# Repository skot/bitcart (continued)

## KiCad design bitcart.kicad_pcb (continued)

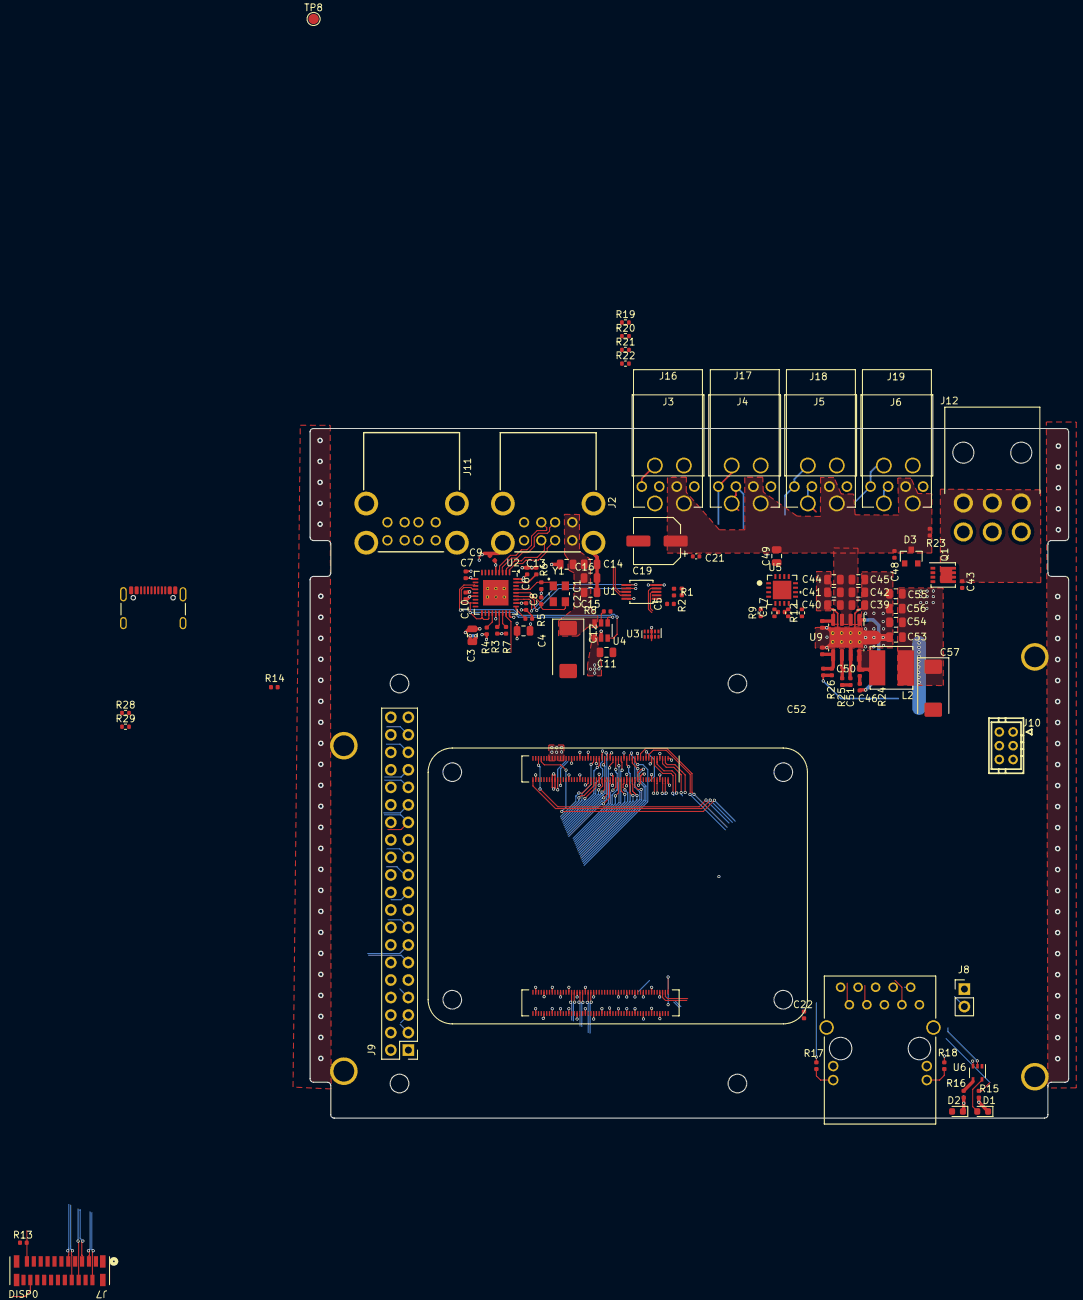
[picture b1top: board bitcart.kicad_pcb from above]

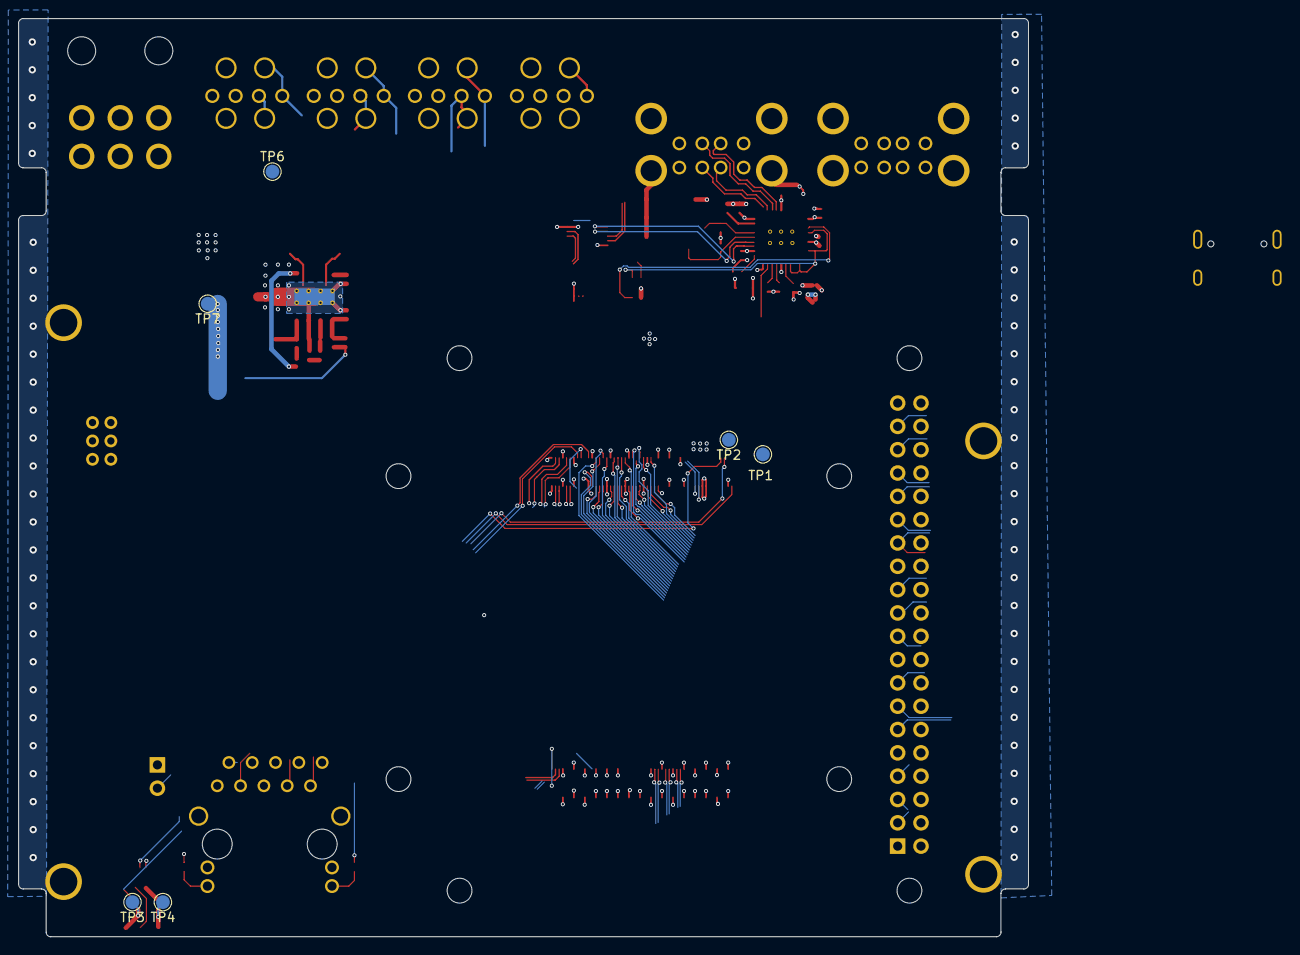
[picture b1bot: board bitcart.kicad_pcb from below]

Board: 4 copper layers, 110.0 x 100.0 mm, 114 parts (6 on the bottom side), 112 nets.

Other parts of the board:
C19: 220uF; CP_Elec_6.3x7.7
C21: 0.1uF; C_0402_1005Metric

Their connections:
/12V: C19.1, C21.1; also elsewhere on the board
GND: C19.2, C21.2; also elsewhere on the board

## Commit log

2023-09-14 initial import -- renamed CM4 IO Board
2023-09-14 added external step files
2023-09-15 removed HDMI, CAM and DISP1 connectors
2023-09-15 added hashboard connectors. added GPU power connector
2023-09-20 extended the board to make room for IO connectors. added the vertical display connector.
2023-09-20 added the PSU control connector.
2023-09-20 remove temp files
2023-10-13 finding/adding digikey part numbers
2023-10-13 added a lot more parts
2023-10-15 added the right board outline. rotated the CM4. switched to single-shroud RA fan connectors
2023-10-15 add render
2023-10-17 resolved some schematic-board errors. switched to tap-on-top ethernet.
2024-02-27 pulled in bitcrane fan and data connectors and edge cuts. most placement done. started routing
2024-02-29 more placement
2024-03-01 lots of routing. lots more to do
2024-03-27 more routing
2024-03-28 added more USB ports.. placing
